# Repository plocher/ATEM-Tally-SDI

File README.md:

# ATEM-Tally-Camera-Light
## License: MIT License

Part 1 of a RFM69-based BlackMagic ATEM Tally Light system - ATEM SDI Interface

Part 1 is the SDI-connected controller
Part 2 is the on-camera tally light display

The controller uses the BMD SDI-Shield as an I2C interface to the control signals embedded in the SDI video stream emitted by the ATEM switchers, connected to an AdaFruit RadioFeather AVR 32u4 RFM69 controller and an AdaFruit neopixel strip.  

The Tally light receivers use the same AdaFruit RadioFeather RFM68 AVR 32U4 sticks with a NeoPixel strip that displays Red (LIVE), Green (PREVIEW) or dim Blue (operational, but not currently selected).

The Arduino IDE sketch is available on GitHub (... TBD URL ...)

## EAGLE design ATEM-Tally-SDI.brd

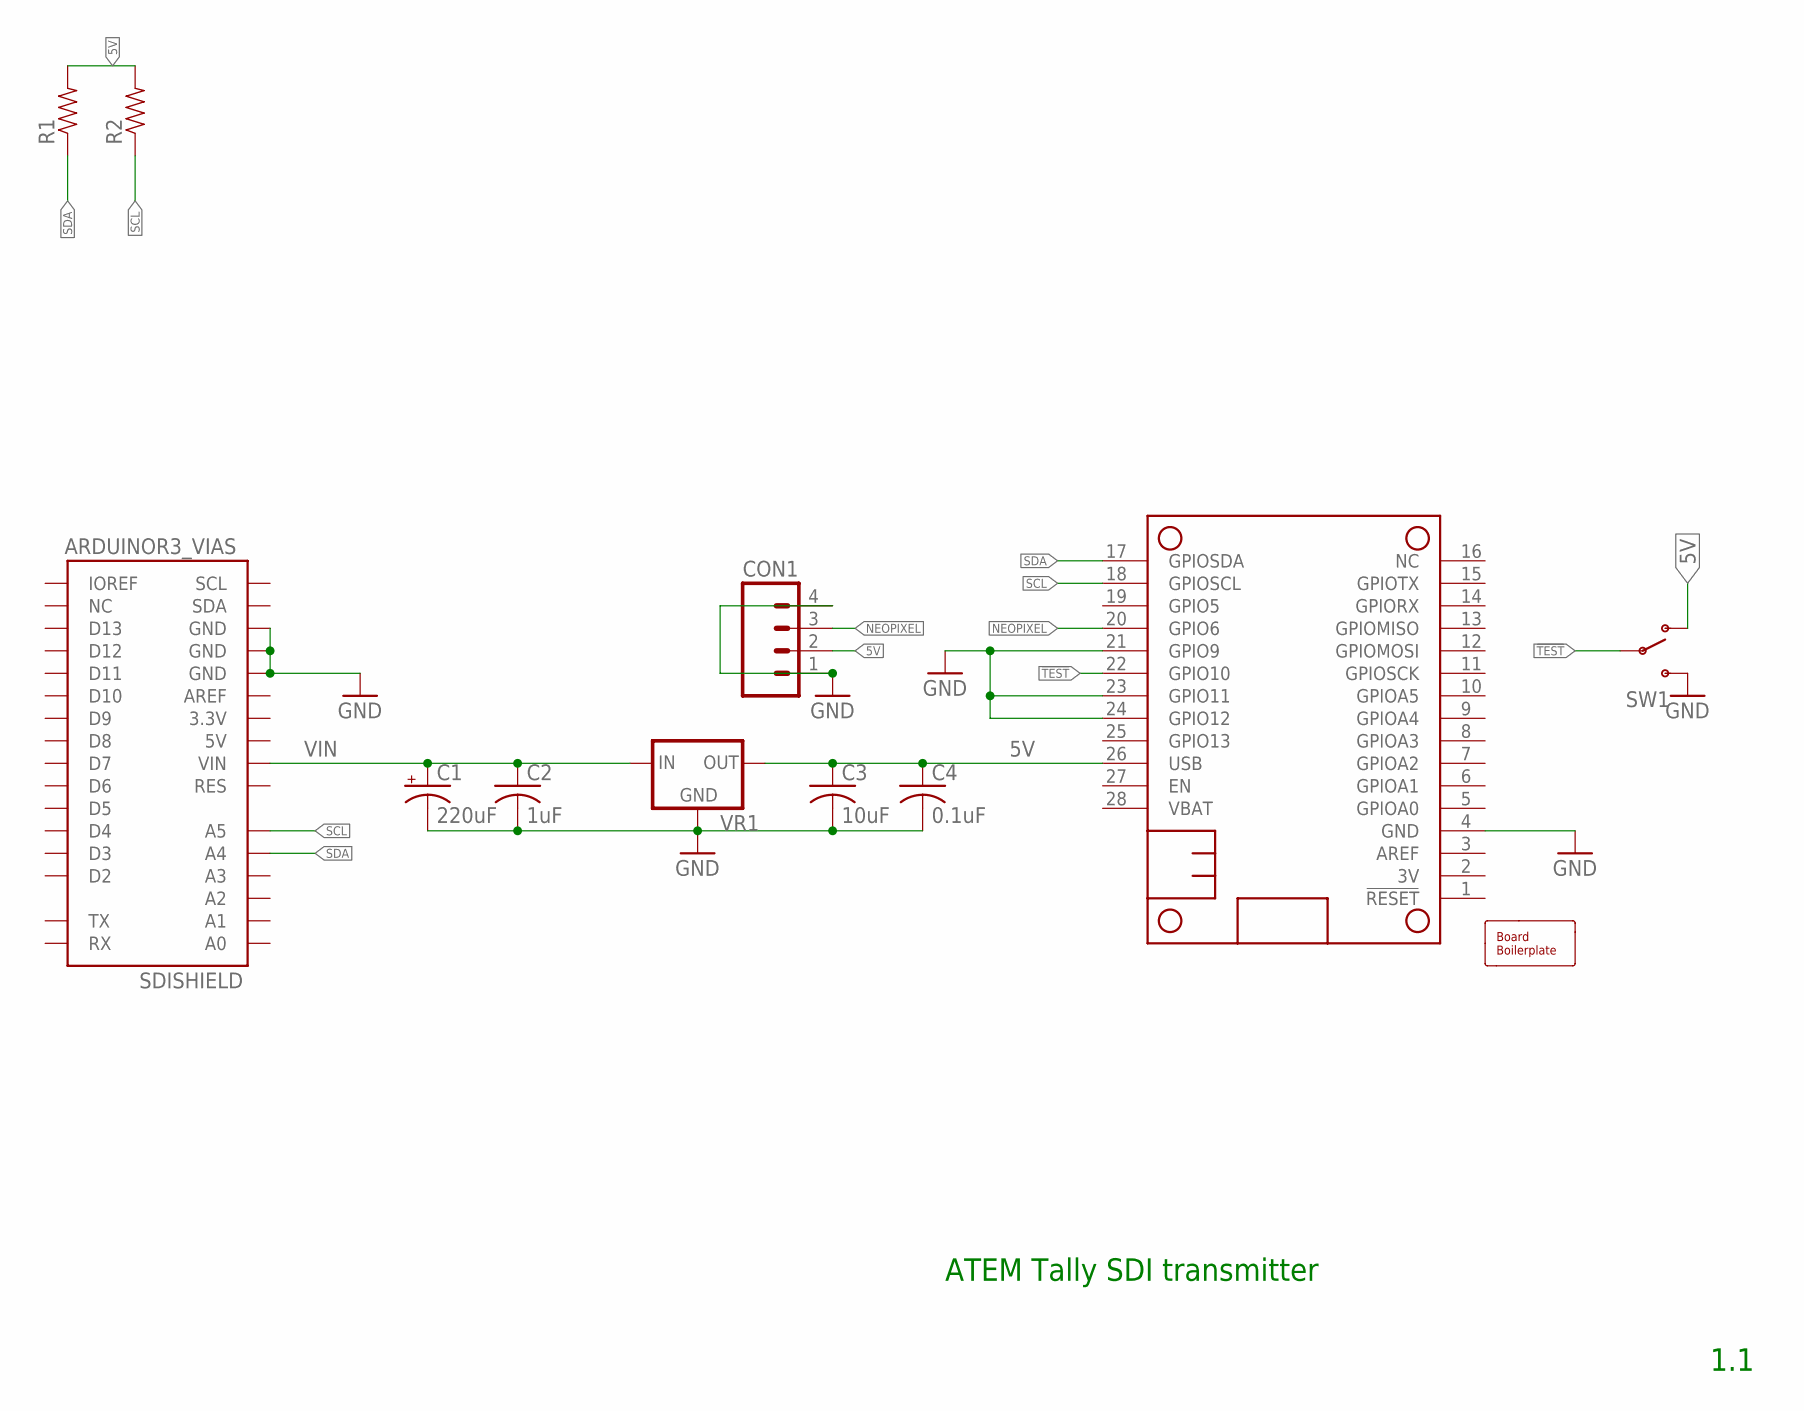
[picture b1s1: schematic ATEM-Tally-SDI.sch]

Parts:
BOARD1: BOARD80X100; BOARD-DINRAIL-3.17INX10CM
C1: 220uF; 0810-CAP
C2: 1uF; 0603-CAP
C3: 10uF; 0603-CAP
C4: 0.1uF; 0603-CAP
CON1: CONNECTOR-M04LOCK; 1X04_LOCK
FEATHER: FEATHERWING_NODIM; FEATHERWING_DIM
R1, R2: RPTH04; AXIAL-0.4-RES
SDISHIELD: ARDUINOR3_VIAS; ARDUINO_R3_VIAS
SW1: SWITCH-SPSTPTH; SWITCH-SPDT
VR1: VREG-DPAK-5; TO-252

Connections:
5V: C3.1, C4.1, CON1.2, FEATHER.26 (USB), R1.P$2 (2), R2.P$2 (2), SW1.1 (O), VR1.3 (OUT)
!TEST: FEATHER.22 (GPIO10), SW1.2
GND: C1.-, C2.2, C3.2, C4.2, CON1.1, CON1.4, FEATHER.4 (GND), FEATHER.21 (GPIO9), FEATHER.23 (GPIO11), FEATHER.24 (GPIO12), SDISHIELD.GND@0 (GND), SDISHIELD.GND@1 (GND), SDISHIELD.GND@2 (GND), SW1.3 (S), VR1.2 (GND)
NEOPIXEL: CON1.3, FEATHER.20 (GPIO6)
SCL: FEATHER.18 (GPIOSCL), R2.P$1 (1), SDISHIELD.A5
SDA: FEATHER.17 (GPIOSDA), R1.P$1 (1), SDISHIELD.A4
VIN: C1.+, C2.1, SDISHIELD.VIN, VR1.1 (IN)

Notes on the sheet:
1.1
ATEM Tally SDI transmitter

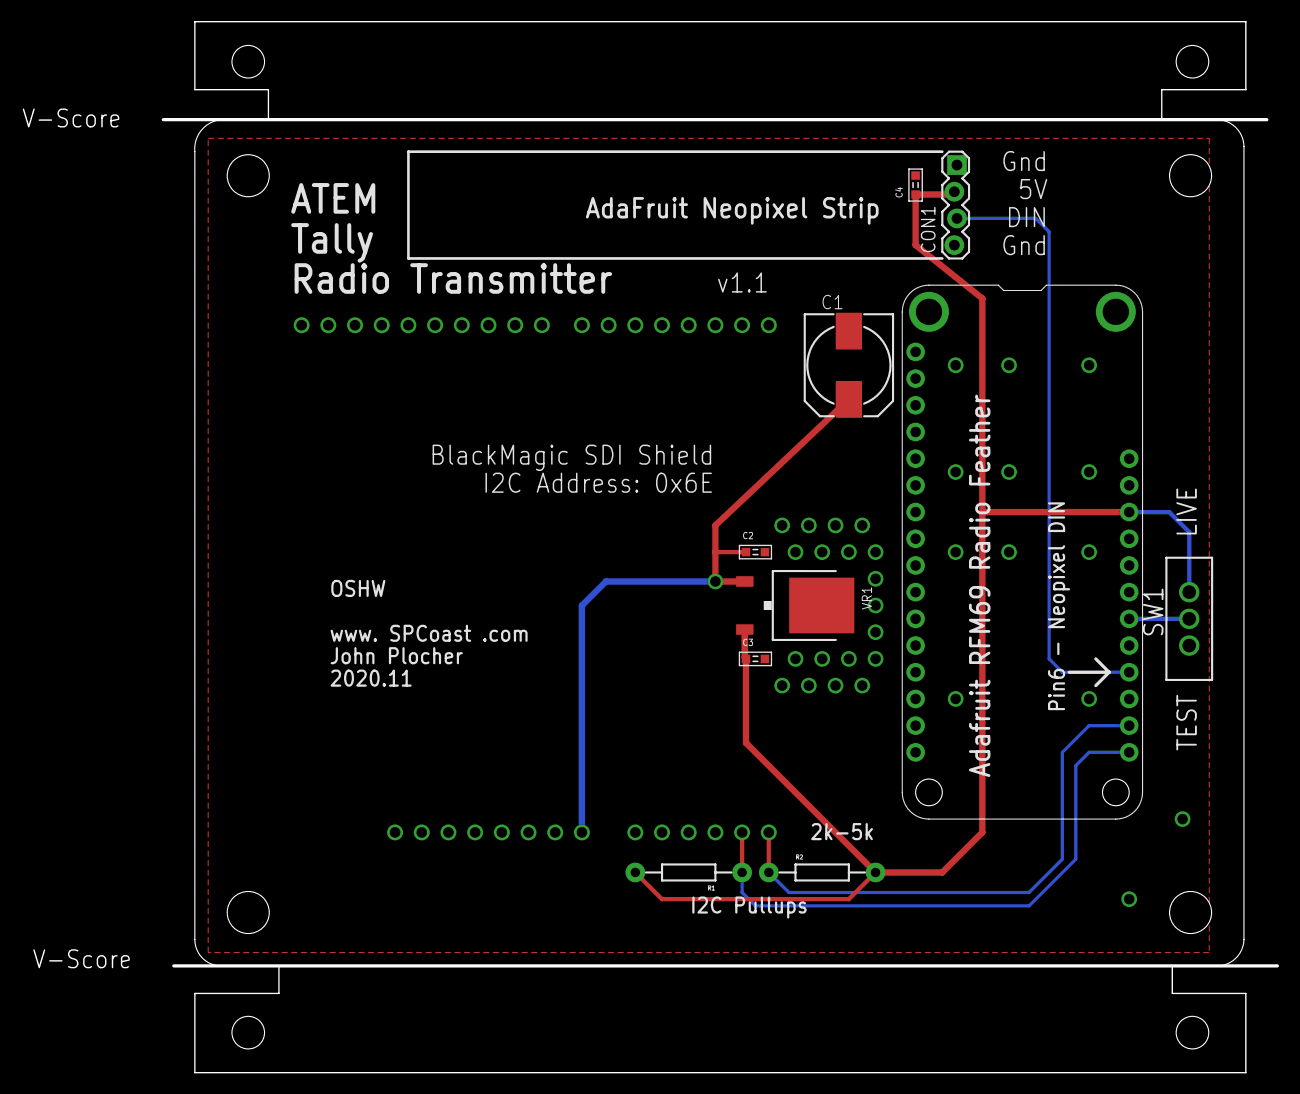
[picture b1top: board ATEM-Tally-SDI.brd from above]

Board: 2 copper layers, 106.0 x 100.0 mm, 12 parts (0 on the bottom side), 7 nets.

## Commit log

2020-10-28 Initial version
2020-11-01 fixed airwires
2020-11-02 Moved Feather to make room for antenna
2020-11-23 revamped options pins
2020-12-13 links
2020-12-13 bugfix
